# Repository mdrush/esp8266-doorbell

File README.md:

# esp8266-doorbell
An internet gateway for a doorbell.

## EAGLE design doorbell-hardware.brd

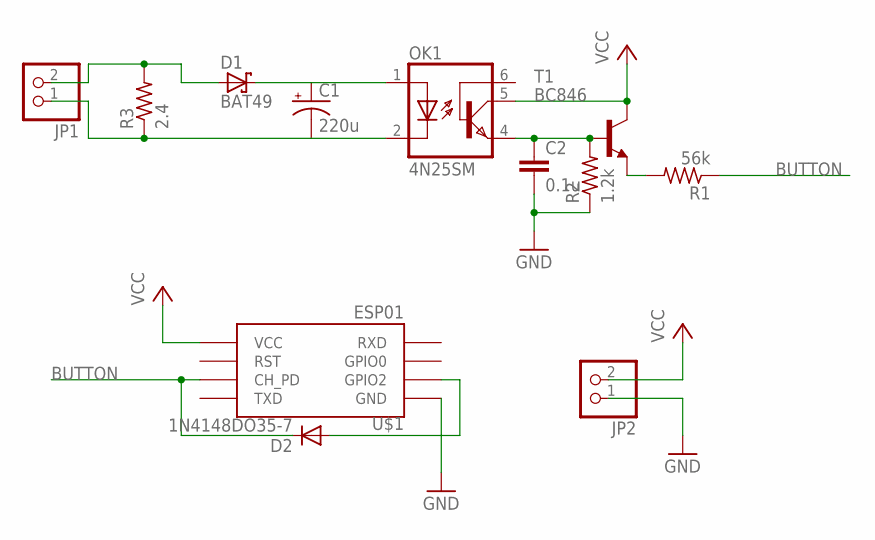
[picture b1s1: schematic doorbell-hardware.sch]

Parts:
C1: 220u; E2-4
C2: 0.1u; C2.5-2
D1: BAT49; DO41-10
D2: 1N4148DO35-7; DO35-7
JP1, JP2: PINHD-1X2; 1X02
OK1: 4N25SM; DIL6-SMD
R1: 56k; 0204/5
R2: 1.2k; 0204/5
R3: 2.4; P0613/15
T1: BC846; SOT23
U$1: ESP01

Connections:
BUTTON: D2.C, R1.1, U$1.CH_PD
GND: C2.2, JP2.1, R2.1, U$1.GND
unnamed: D1.A, JP1.2, R3.2
unnamed: R1.2, T1.2 (E)
unnamed: C1.+, D1.C, OK1.1 (A)
unnamed: C1.-, JP1.1, OK1.2 (C), R3.1
unnamed: C2.1, OK1.4 (EMI), R2.2, T1.1 (B)
unnamed: D2.A, U$1.GPIO2
VCC: JP2.2, OK1.5 (COL), T1.3 (C), U$1.VCC

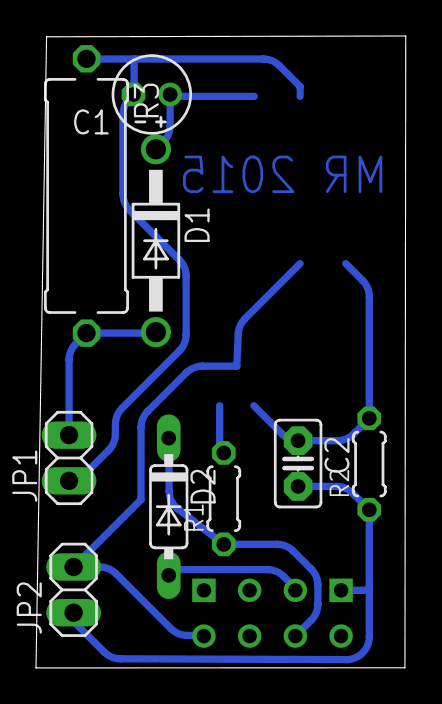
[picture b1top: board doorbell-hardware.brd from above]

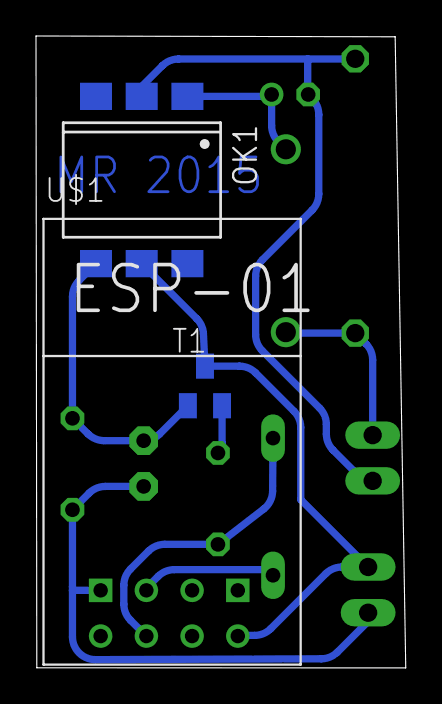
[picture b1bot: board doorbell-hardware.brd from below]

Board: 2 copper layers, 20.5 x 35.1 mm, 12 parts (3 on the bottom side), 9 nets.

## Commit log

2015-11-11 Initial commit, basic hardware schematic done
2015-11-11 Replaced zener with ldo, started work on sleep and interrupt
2015-11-19 simplified circuit and code
2015-11-29 Working code
2015-11-29 Working schematic and smaller layout
2016-02-28 simplified detection circuit
